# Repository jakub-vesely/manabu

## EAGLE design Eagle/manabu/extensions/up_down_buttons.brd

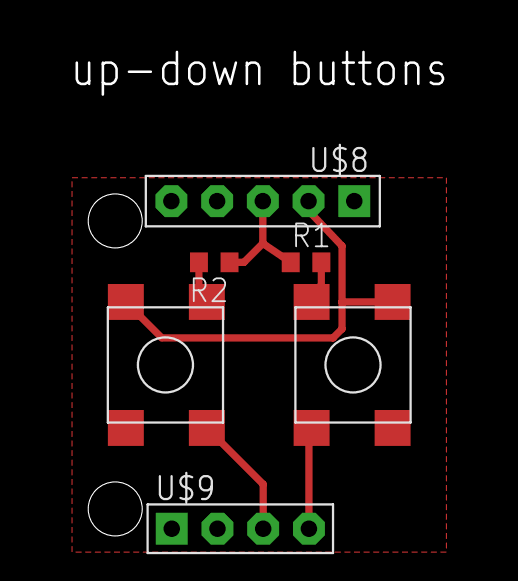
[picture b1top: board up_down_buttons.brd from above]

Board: 2 copper layers, 6 parts (0 on the bottom side), 4 nets.

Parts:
R1, R2: 100k; R0603
U$1, U$2: BUTTON_6.3X6.3; BUTTON_6.2X6.2
U$8: JUMPER5M
U$9: JUMPER4M

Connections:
GND: R1.1, R2.1, U$8.3
unnamed: R2.2, U$2.P$2, U$2.P$4, U$9.3
unnamed: U$1.P$1, U$1.P$3, U$2.P$1, U$2.P$3, U$8.2
unnamed: R1.2, U$1.P$2, U$1.P$4, U$9.4

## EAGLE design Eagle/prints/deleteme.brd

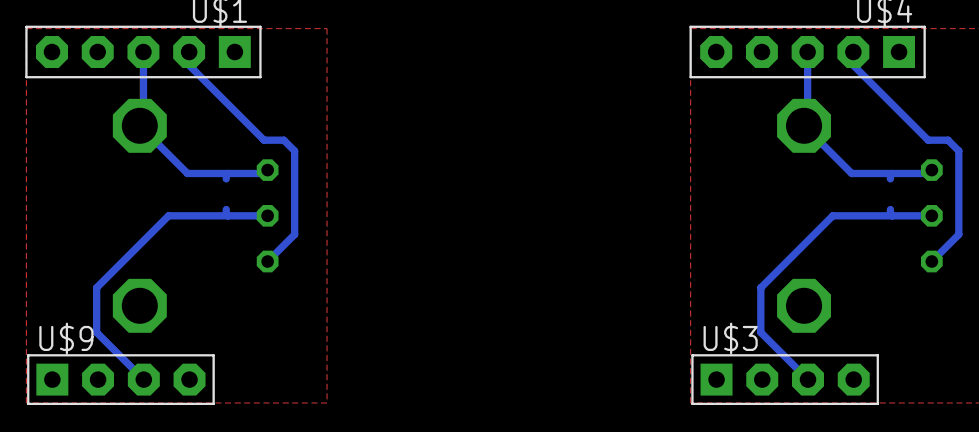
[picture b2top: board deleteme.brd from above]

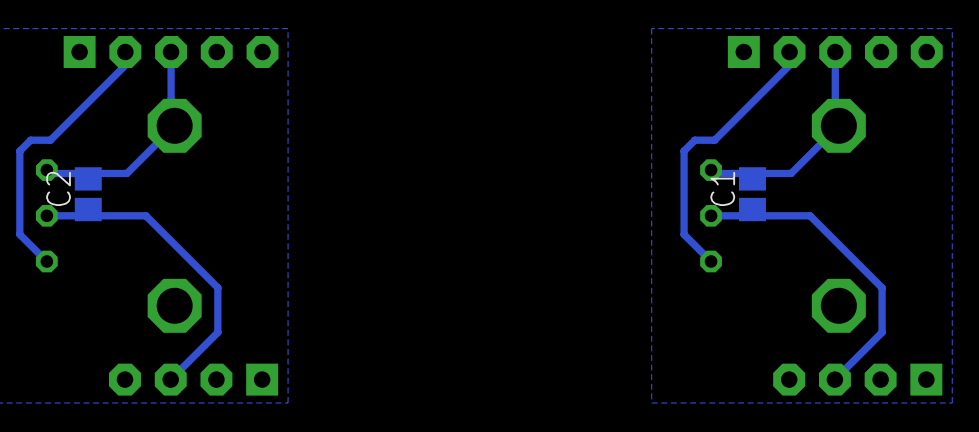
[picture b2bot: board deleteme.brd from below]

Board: 2 copper layers, 8 parts (2 on the bottom side), 6 nets.

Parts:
C1, C2: 100 nF; C0805
U$1, U$4: JUMPER5M
U$2, U$5: POTENTIOMETER-RK09
U$3, U$9: JUMPER4M

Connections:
GND: C1.2, U$1.3, U$2.1, U$2.GND1, U$2.GND2
GND1: C2.2, U$4.3, U$5.1, U$5.GND1, U$5.GND2
unnamed: C1.1, U$2.2, U$9.3
unnamed: U$1.2, U$2.3
unnamed: C2.1, U$3.3, U$5.2
unnamed: U$4.2, U$5.3

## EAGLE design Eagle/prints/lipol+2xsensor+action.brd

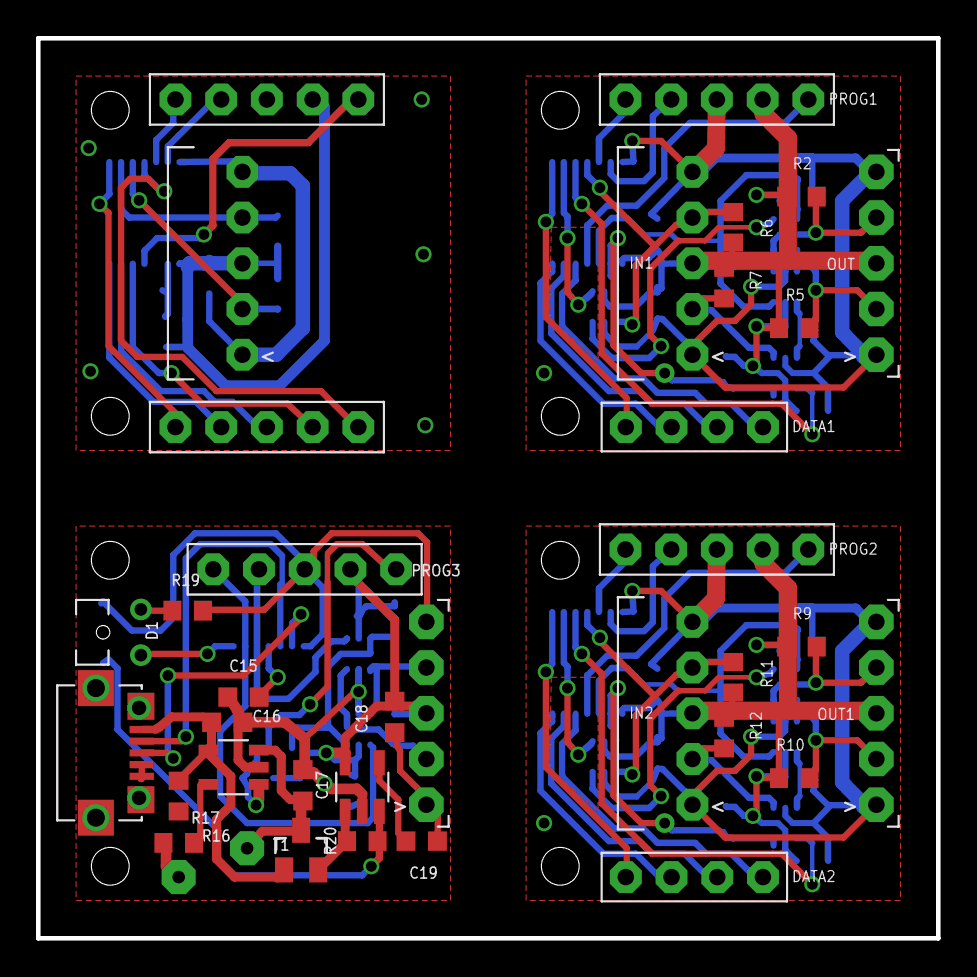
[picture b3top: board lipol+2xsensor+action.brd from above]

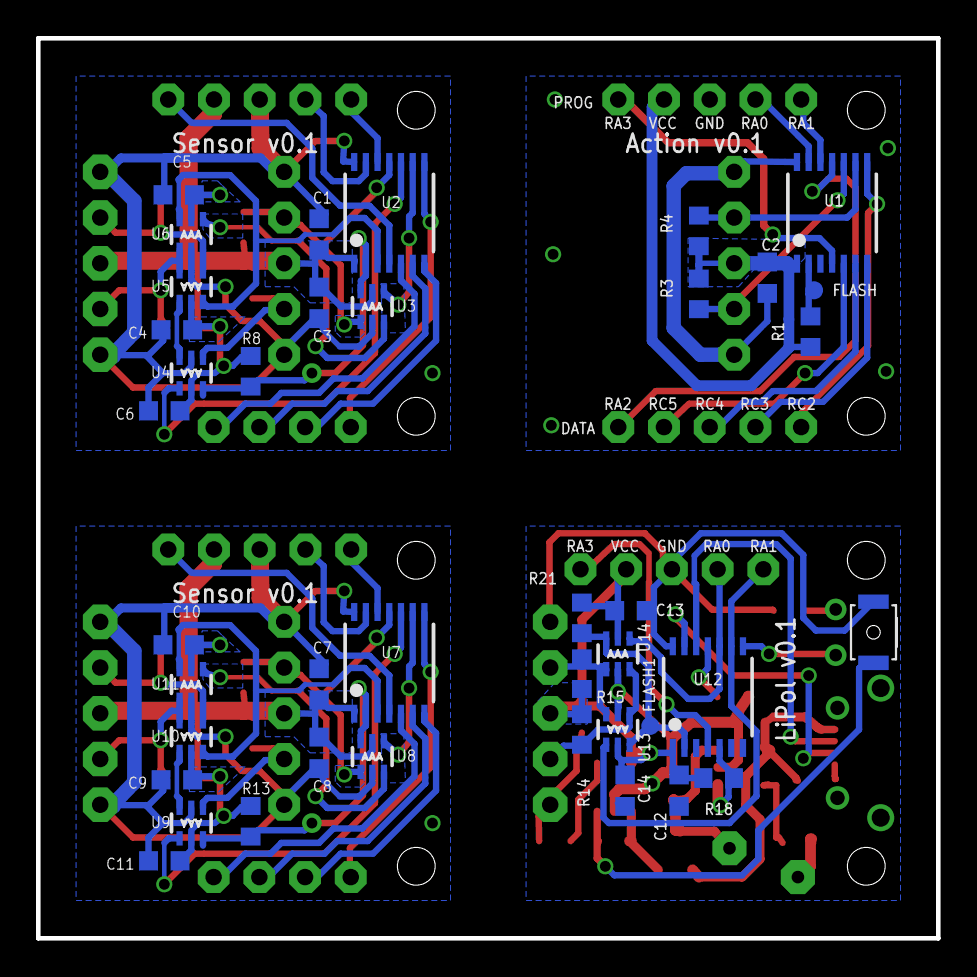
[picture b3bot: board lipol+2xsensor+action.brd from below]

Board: 2 copper layers, 50.0 x 50.0 mm, 76 parts (40 on the bottom side), 71 nets.

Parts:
C1, C2, C3, C4, C5, C6, C7, C8, C9, C10, C11, C12, C13, C14, C15: 100n; C0603K
C16, C17, C18: 4.7u; C0603K
C19: 470p; C0603K
D1: LED1.8
DATA: JUMPER5M
DATA1, DATA2: JUMPER4M
FLASH, FLASH1: TPTP10R; TP10R
IN, IN1, IN2: JUMPER5M-90
MCP73832: MCP73831; SOT23-5
OUT, OUT1, OUT2: JUMPER5F-90
PROG, PROG1, PROG2, PROG3: JUMPER5M
R1, R8, R13, R17, R18, R20, R21: 100k; R0603
R2, R4, R5, R7, R9, R10, R12, R14, R15, R19: 2k2; R0603
R3, R6, R11: 2K2; R0603
R16: 22k; R0603
RESET: BYTTON-B3U; BUTTON-B3U
T1: FDV304P; SOT23
TC1185: TC1185; SOT32-5
U1, U2, U7: 16F103; TSSOP14
U3, U4, U5, U6, U8, U9, U10, U11, U13, U14: NC7SB3157P6X; SC70-6L
U12: 16F1454; TSSOP14
U$3: LIPOL_21X17
USB: USBMICRO; MICROUSB-MOLEX

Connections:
GND: C2.2, IN.1, IN.5, PROG.3, U1.14
GND11: C1.2, C3.2, C4.1, C5.1, C6.2, IN1.1, IN1.5, OUT.1, OUT.5, PROG1.3, U2.14, U3.2, U4.2, U5.2, U6.2
GND12: C7.2, C8.2, C9.1, C10.1, C11.2, IN2.1, IN2.5, OUT1.1, OUT1.5, PROG2.3, U7.14, U8.2, U9.2, U10.2, U11.2
GND13: C12.2, C13.1, C14.1, C15.2, C16.1, C17.1, C18.1, C19.1, MCP73832.2, OUT2.1, OUT2.5, PROG3.3, R16.1, R17.1, R19.1, RESET.P$1, TC1185.GND, U12.14, U13.2, U14.2, U$3.GND, USB.GND, USB.GND1, USB.GND2, USB.GND3, USB.GND4, USB.NC, USB.P$1, USB.P$2, USB.P$3, USB.P$6
unnamed: IN.2, R3.1, U1.10
unnamed: DATA.2, U1.7
unnamed: FLASH.TP, R1.2, U1.2
unnamed: IN.4, R4.1, U1.9
unnamed: PROG1.1, U2.4
unnamed: PROG1.4, U2.13
unnamed: PROG1.5, U2.12
unnamed: IN1.4, R6.1, U2.11, U3.1
unnamed: DATA.5, U1.11
unnamed: DATA.4, U1.5
unnamed: PROG.1, U1.4
unnamed: PROG.4, U1.13
unnamed: PROG.5, U1.12
unnamed: DATA.3, U1.6
unnamed: DATA.1, U1.8
unnamed: DATA1.1, U2.8
unnamed: DATA1.3, U2.6
unnamed: DATA1.4, U2.5
unnamed: R8.1, U2.2, U3.6, U4.6
unnamed: OUT.2, R5.1, U5.3, U6.1
unnamed: OUT.4, R2.1, U5.1, U6.3
unnamed: IN1.2, R7.1, U4.1
unnamed: U4.3, U5.4
unnamed: U3.3, U6.4
unnamed: U2.3, U5.6, U6.6
unnamed: U2.10, U4.4
unnamed: U2.9, U3.4
unnamed: DATA1.2, U2.7
unnamed: PROG2.1, U7.4
unnamed: PROG2.4, U7.13
unnamed: PROG2.5, U7.12
unnamed: IN2.4, R11.1, U7.11, U8.1
unnamed: DATA2.1, U7.8
unnamed: DATA2.3, U7.6
unnamed: DATA2.4, U7.5
unnamed: R13.1, U7.2, U8.6, U9.6
unnamed: OUT1.2, R10.1, U10.3, U11.1
unnamed: OUT1.4, R9.1, U10.1, U11.3
unnamed: IN2.2, R12.1, U9.1
unnamed: U9.3, U10.4
unnamed: U8.3, U11.4
unnamed: U7.3, U10.6, U11.6
unnamed: U7.10, U9.4
unnamed: U7.9, U8.4
unnamed: DATA2.2, U7.7
unnamed: OUT2.4, R15.1, U13.3, U14.1
unnamed: OUT2.2, R14.1, U13.1, U14.3
unnamed: PROG3.5, U12.9, U13.4
unnamed: FLASH1.TP, R21.2, U12.2, U13.6, U14.6
unnamed: U12.12, USB.D-
unnamed: U12.13, USB.D+
unnamed: C15.1, U12.11
unnamed: PROG3.4, U12.10, U14.4
unnamed: C17.2, MCP73832.3, T1.D, U$3.VBAT
unnamed: C16.2, MCP73832.4, R17.2, T1.G, USB.VUSB
unnamed: MCP73832.5, R16.2
unnamed: R20.1, T1.S, TC1185.VIN
unnamed: MCP73832.1, R18.2, U12.5
unnamed: PROG3.1, U12.4
unnamed: D1.K, R19.2
unnamed: D1.A, U12.8
unnamed: C19.2, TC1185.BP
unnamed: R20.2, RESET.P$2, TC1185.SHDN
VCC: C2.1, IN.3, PROG.2, R1.1, R3.2, R4.2, U1.1
VCC1: C1.1, C3.1, C4.2, C5.2, C6.1, IN1.3, OUT.3, PROG1.2, R2.2, R5.2, R6.2, R7.2, R8.2, U2.1, U3.5, U4.5, U5.5, U6.5
VCC2: C7.1, C8.1, C9.2, C10.2, C11.1, IN2.3, OUT1.3, PROG2.2, R9.2, R10.2, R11.2, R12.2, R13.2, U7.1, U8.5, U9.5, U10.5, U11.5
VCC3: C12.1, C13.2, C14.2, C18.2, OUT2.3, PROG3.2, R14.2, R15.2, R18.1, R21.1, TC1185.VOUT, U12.1, U13.5, U14.5

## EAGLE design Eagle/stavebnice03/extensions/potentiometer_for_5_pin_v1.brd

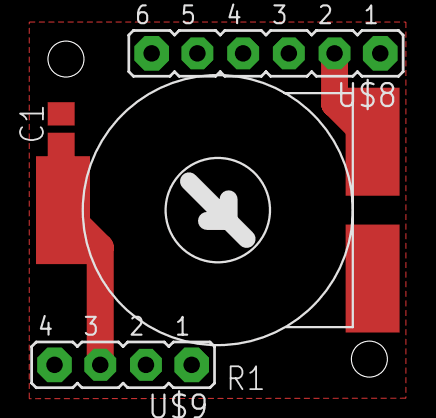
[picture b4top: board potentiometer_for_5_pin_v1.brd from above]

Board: 2 copper layers, 4 parts (0 on the bottom side), 3 nets.

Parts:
C1: 100 nF; C0805
R1: 10 k; R-TRIM
U$8: JUMPER6M
U$9: JUMPER4M

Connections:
GND: C1.2, R1.1, U$8.1, U$8.3, U$8.4, U$8.5, U$8.6, U$9.1, U$9.2, U$9.4
unnamed: C1.1, R1.2, U$9.3
unnamed: R1.3, U$8.2

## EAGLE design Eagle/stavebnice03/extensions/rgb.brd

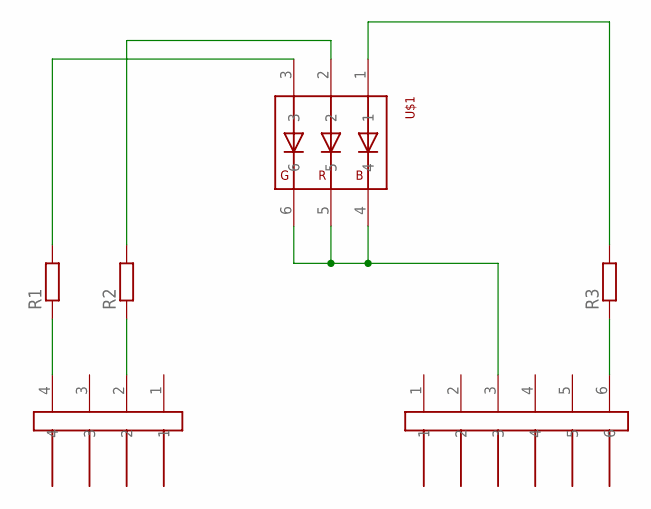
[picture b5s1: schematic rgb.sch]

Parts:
R1, R2, R3: R-EU_R0603; R0603
U$1: RGB_WW-FCE50TC-Q1
U$8: JUMPER6M
U$9: JUMPER4M

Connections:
GND: U$1.4, U$1.5, U$1.6, U$8.3
unnamed: R1.1, U$9.4
unnamed: R1.2, U$1.3
unnamed: R2.2, U$1.2
unnamed: R3.2, U$1.1
unnamed: R2.1, U$9.2
unnamed: R3.1, U$8.6

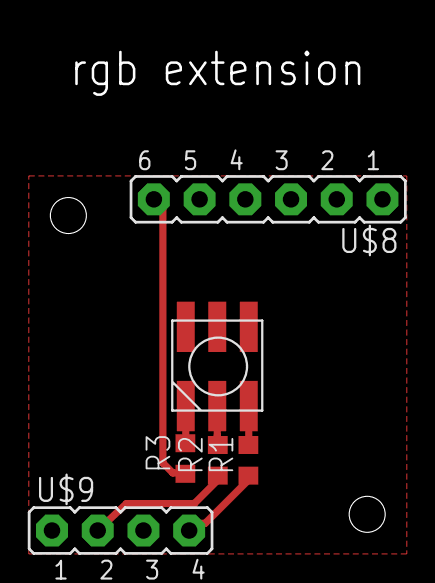
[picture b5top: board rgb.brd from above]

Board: 2 copper layers, 6 parts (0 on the bottom side), 7 nets.

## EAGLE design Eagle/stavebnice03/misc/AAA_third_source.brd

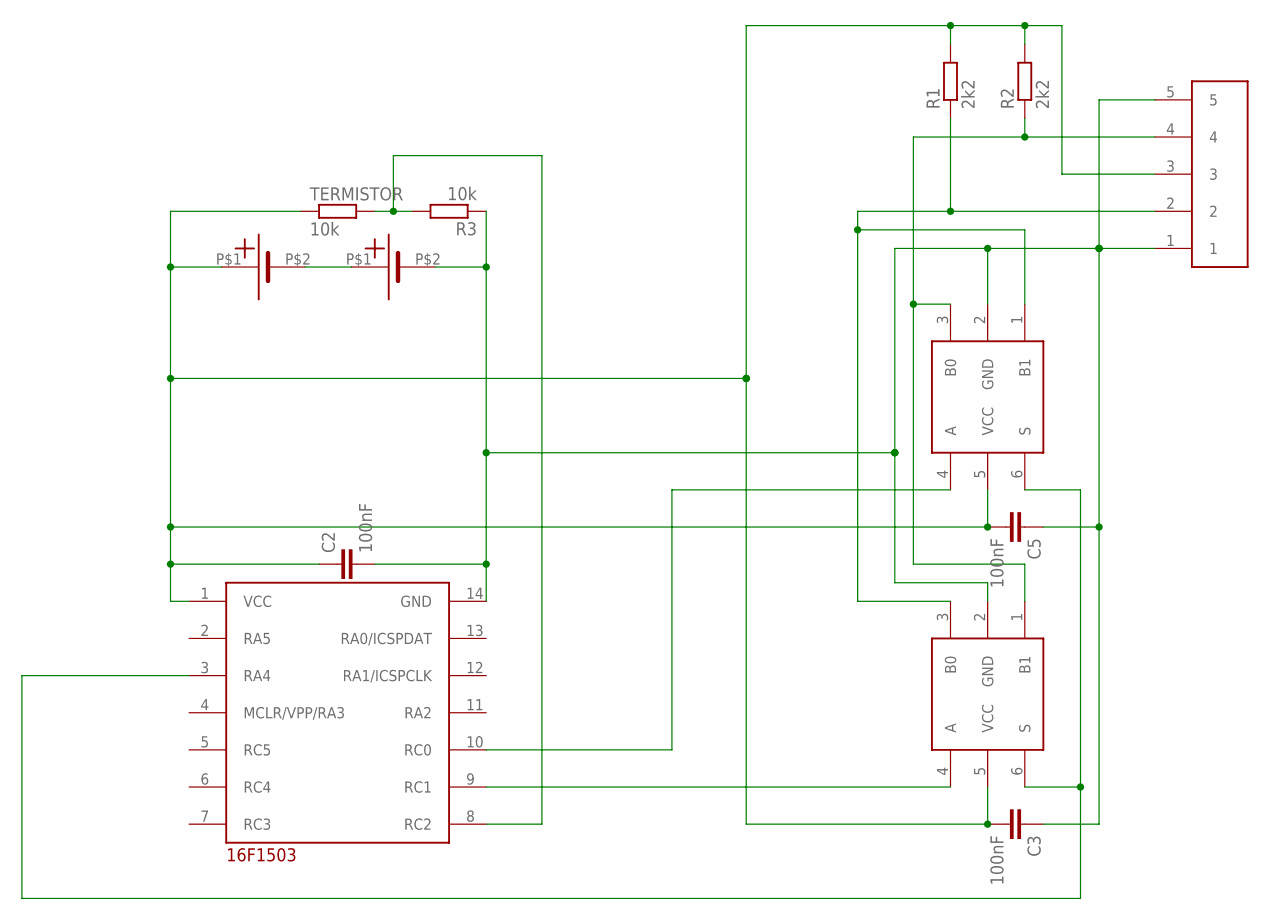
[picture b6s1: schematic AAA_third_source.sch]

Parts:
C2, C3, C5: 100nF; C0603
R1, R2: 2k2; R0603
R3: 10k; R0603
TERMISTOR: 10k; R0603
U$1: 16F103-TSSOP; TSSOP14
U$2, U$3: AAA_THIRD
U$5: JUMPER5F-90
U$6, U$7: NC7SB3157P6X; SC70-6L

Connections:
GND: C2.2, C3.1, C5.1, R3.1, U$1.14 (GND), U$3.P$2 ($2), U$5.1, U$5.5, U$6.2 (GND), U$7.2 (GND)
unnamed: U$1.3 (RA4), U$6.6 (S), U$7.6 (S)
unnamed: U$2.P$2 ($2), U$3.P$1 ($1)
unnamed: R3.2, TERMISTOR.2, U$1.8 (RC2)
unnamed: U$1.9 (RC1), U$7.4 (A)
unnamed: R1.1, U$5.2, U$6.1 (B1), U$7.3 (B0)
unnamed: U$1.10 (RC0), U$6.4 (A)
unnamed: R2.1, U$5.4, U$6.3 (B0), U$7.1 (B1)
VCC: C2.1, C3.2, C5.2, R1.2, R2.2, TERMISTOR.1, U$1.1 (VCC), U$2.P$1 ($1), U$5.3, U$6.5 (VCC), U$7.5 (VCC)

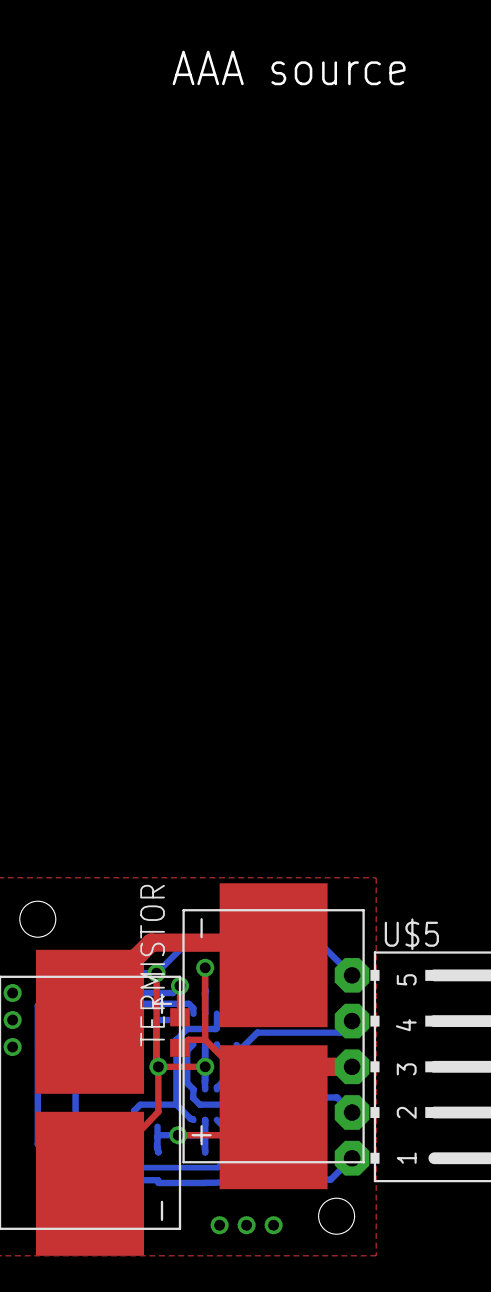
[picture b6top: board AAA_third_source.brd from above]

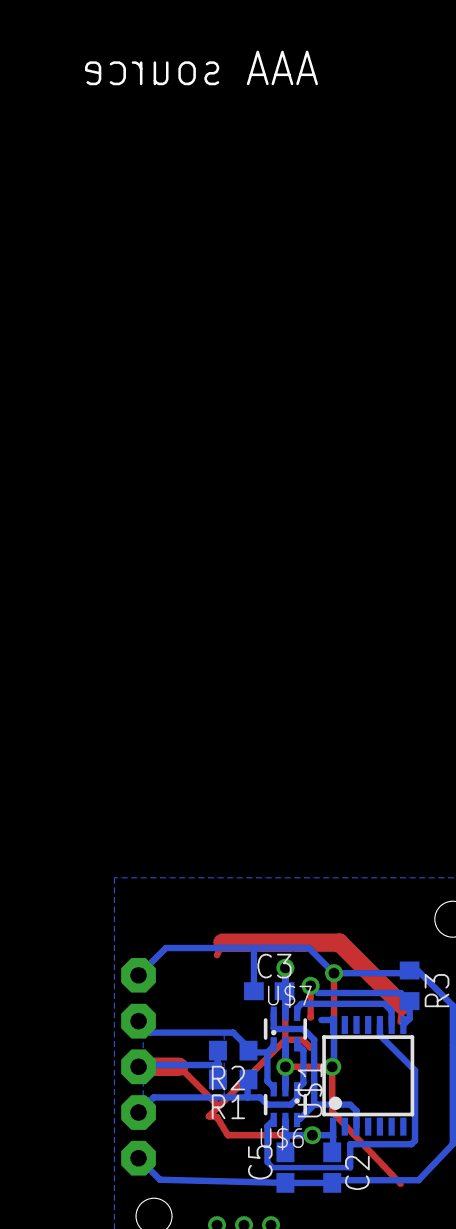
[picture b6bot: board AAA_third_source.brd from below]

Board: 2 copper layers, 13 parts (9 on the bottom side), 9 nets.
